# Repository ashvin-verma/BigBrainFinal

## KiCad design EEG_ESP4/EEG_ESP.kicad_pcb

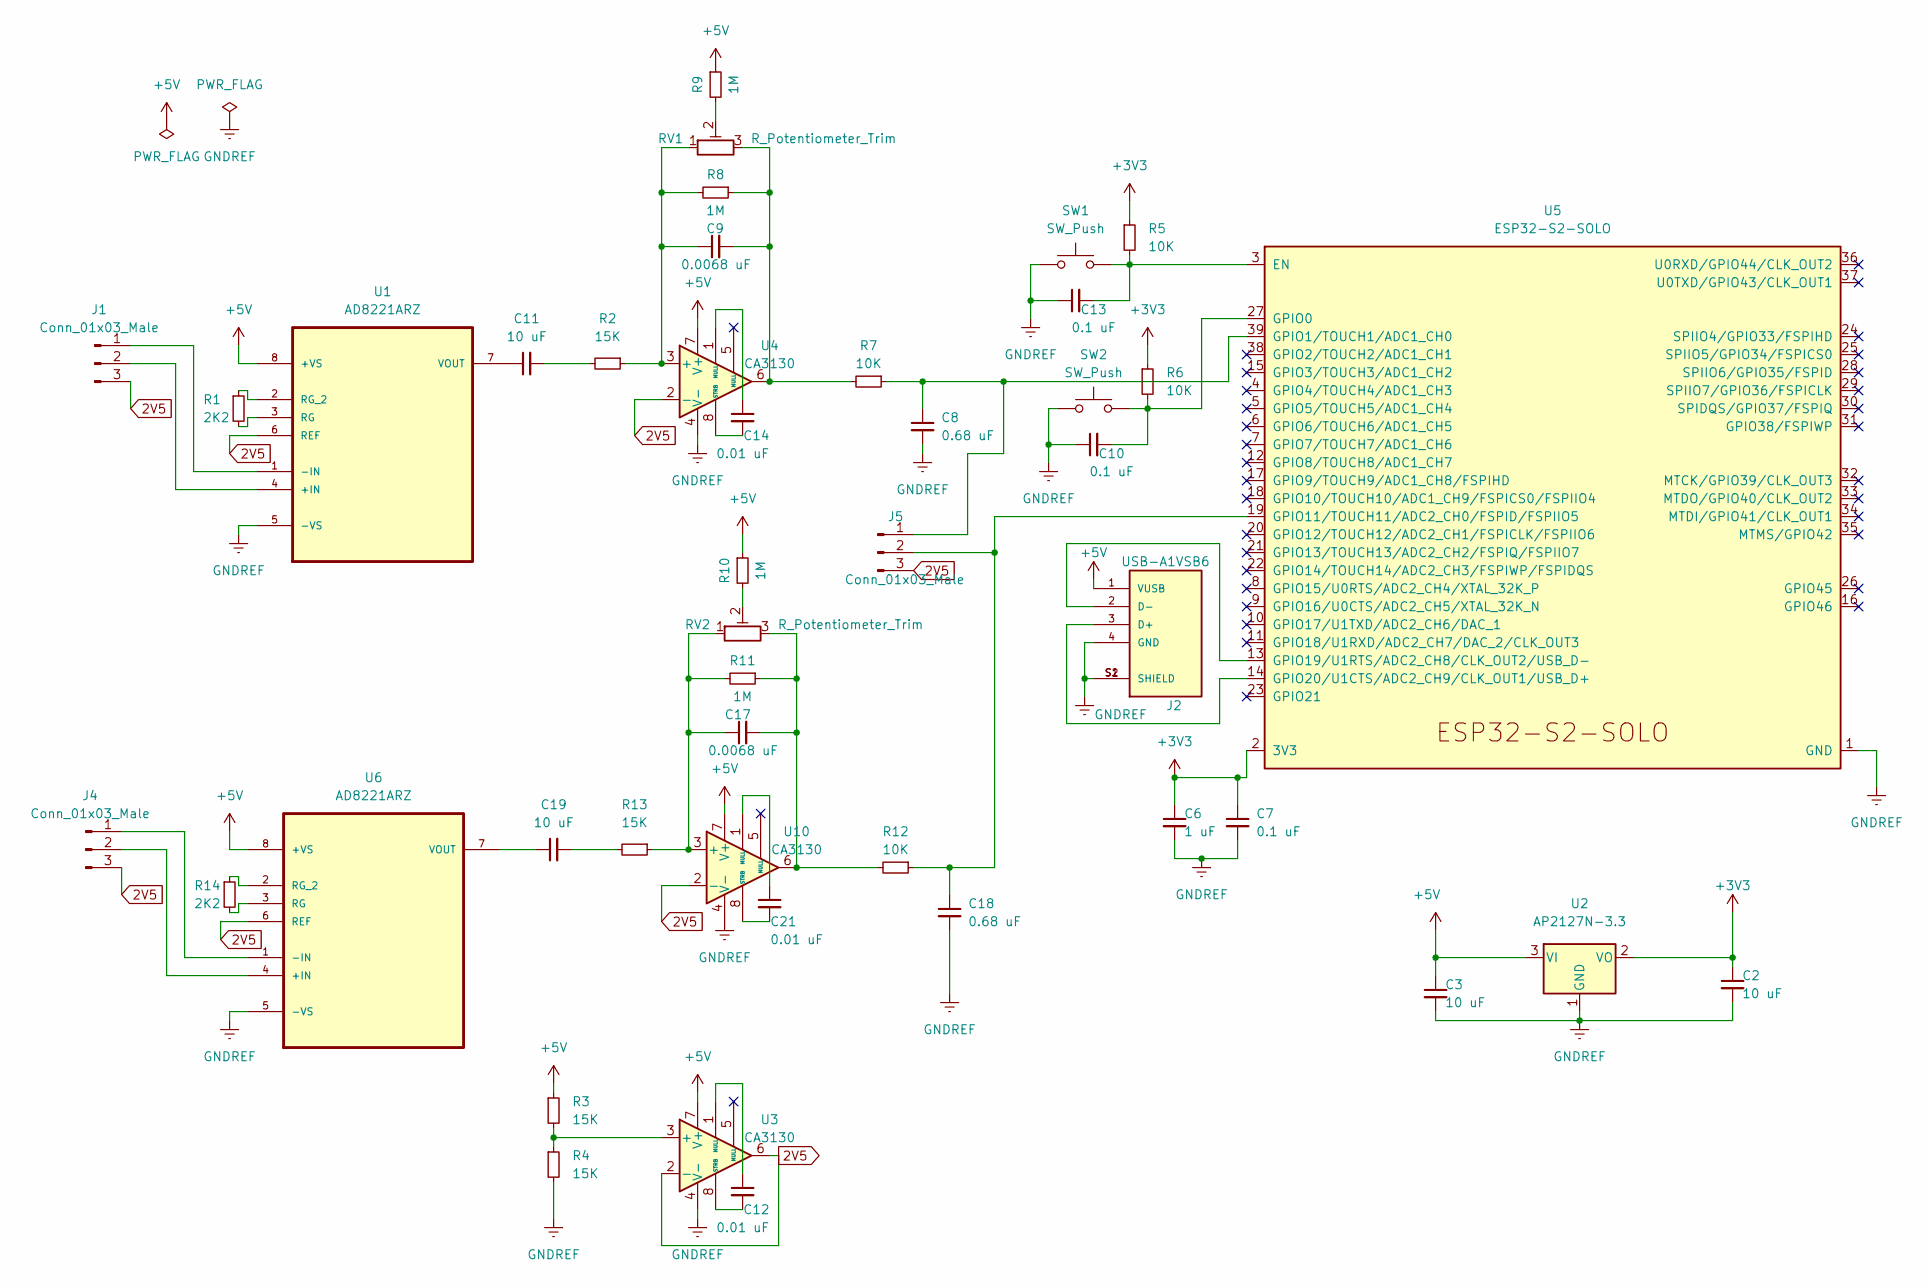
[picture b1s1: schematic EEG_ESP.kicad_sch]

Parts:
C2, C3, C11, C19: 10 uF; C_0603_1608Metric
C6: 1 uF; C_0603_1608Metric
C7, C10, C13: 0.1 uF; C_0603_1608Metric
C8, C18: 0.68 uF; C_0603_1608Metric
C9, C17: 0.0068 uF; C_0603_1608Metric
C12, C14, C21: 0.01 uF; C_0603_1608Metric
J1, J4, J5: Conn_01x03_Male; 61300311121
J2: USB-A1VSB6; ONSHORE_USB-A1VSB6; PARTREV D
R1, R14: 2K2; R_0603_1608Metric
R2, R3, R4, R13: 15K; R_0603_1608Metric
R5, R6, R7, R12: 10K; R_0603_1608Metric
R8, R9, R10, R11: 1M; R_0603_1608Metric
RV1, RV2: R_Potentiometer_Trim; Potentiometer_Bourns_3314G_Vertical
SW1, SW2: SW_Push; ESB-33535A
U1, U6: AD8221ARZ; SOIC127P600X175-8N; MPN AD8221ARZ
U2: AP2127N-3.3; SOT91P240X110-3N
U3, U4, U10: CA3130; SOIC-8-1EP_3.9x4.9mm_P1.27mm_EP2.29x3mm
U5: ESP32-S2-SOLO

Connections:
2V5: J1.3, J4.3, J5.3, U1.6 (REF), U3.2 (-), U3.6, U4.2 (-), U6.6 (REF), U10.2 (-)
+3V3: C2.1, C6.1, C7.1, R5.1, R6.1, U2.2 (VO), U5.2 (3V3)
+5V: C3.1, J2.1 (VUSB), R3.1, R9.1, R10.1, U1.8 (+VS), U2.3 (VI), U3.7 (V+), U4.7 (V+), U6.8 (+VS), U10.7 (V+)
GNDREF: C2.2, C3.2, C6.2, C7.2, C8.2, C10.1, C13.1, C18.2, J2.4 (GND), J2.S1 (SHIELD), J2.S2 (SHIELD), R4.2, SW1.1, SW2.1, U1.5 (-VS), U2.1 (GND), U3.4 (V-), U4.4 (V-), U5.1 (GND), U5.40 (GND), U5.41 (GND), U6.5 (-VS), U10.4 (V-)
unnamed: C8.1, J5.1, R7.1, U5.39 (GPIO1/TOUCH1/ADC1_CH0)
unnamed: C9.1, R2.1, R8.2, RV1.1, U4.3 (+)
unnamed: C9.2, R7.2, R8.1, RV1.3, U4.6
unnamed: C10.2, R6.2, SW2.2, U5.27 (GPIO0)
unnamed: C11.1, U1.7 (VOUT)
unnamed: C11.2, R2.2
unnamed: C12.1, U3.1 (NULL)
unnamed: C12.2, U3.8 (STRB)
unnamed: C13.2, R5.2, SW1.2, U5.3 (EN)
unnamed: C14.1, U4.1 (NULL)
unnamed: C14.2, U4.8 (STRB)
unnamed: C17.1, R11.2, R13.1, RV2.1, U10.3 (+)
unnamed: C17.2, R11.1, R12.2, RV2.3, U10.6
unnamed: C19.1, U6.7 (VOUT)
unnamed: C19.2, R13.2
unnamed: C21.1, U10.1 (NULL)
unnamed: C21.2, U10.8 (STRB)
unnamed: J1.1, U1.1 (-IN)
unnamed: J1.2, U1.4 (+IN)
unnamed: J2.2 (D-), U5.13 (GPIO19/U1RTS/ADC2_CH8/CLK_OUT2/USB_D-)
unnamed: J2.3 (D+), U5.14 (GPIO20/U1CTS/ADC2_CH9/CLK_OUT1/USB_D+)
unnamed: J4.1, U6.1 (-IN)
unnamed: J4.2, U6.4 (+IN)
unnamed: R3.2, R4.1, U3.3 (+)
unnamed: R9.2, RV1.2
unnamed: R10.2, RV2.2
unnamed: R1.1, U1.2 (RG_2)
unnamed: R1.2, U1.3 (RG)
unnamed: R14.1, U6.2 (RG_2)
unnamed: R14.2, U6.3 (RG)

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
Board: 2 copper layers, 43 parts (0 on the bottom side), 35 nets, no tracks yet.

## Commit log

2024-05-03 progress at end of hope

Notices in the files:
parts and their libraries:
Copyright 2021 Accelerated Designs. All rights reserved.
